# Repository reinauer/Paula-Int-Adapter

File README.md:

# Paula Interrupt Adapter

This is an Interrupt Adapter for the Amiga 500/2000 version of Paula.

## About

This adapter is an el cheapo version of the Action Replay. In connection with
the HRTMon software you can enter a debugger / monitor at any time while your
software is running, and mess around with all of memory (infinite lives, yay!)

## But Why?

I probably started getting into soldering because I wanted to have one of
[highpuff's INT7 adapters](https://www.ikod.se/a1200-600-int7/) but I could
not buy one from him, simply because the cost of shipping across the Atlantic
Ocean would by far exceed the value of the adapter. So I ordered a few PCBs
from across the Pacific instead and started soldering PLCC-52 sockets and
diodes.

Now, a few months later, I also got an Amiga 500 in my collection, and there
didn't seem to be a solution like highpuff's adapter available for the most
popular of all Amigas. So, I decided to make one.

## Bill of Materials

Here's the [Bill of Materials (BOM)](https://htmlpreview.github.io/?https://raw.githubusercontent.com/reinauer/Paula-Int-Adapter/main/bom.html).

## Make your own

* [PCBWay](https://www.pcbway.com/project/shareproject/Paula_Interrupt_Adapter__A500_A2000_.html)
* [OSHpark](https://oshpark.com/shared_projects/0WhlMhrr)

## Credits

Big thanks to djbase for the inspiration and to highpuff for the A1200/A4000
INT7 adapter

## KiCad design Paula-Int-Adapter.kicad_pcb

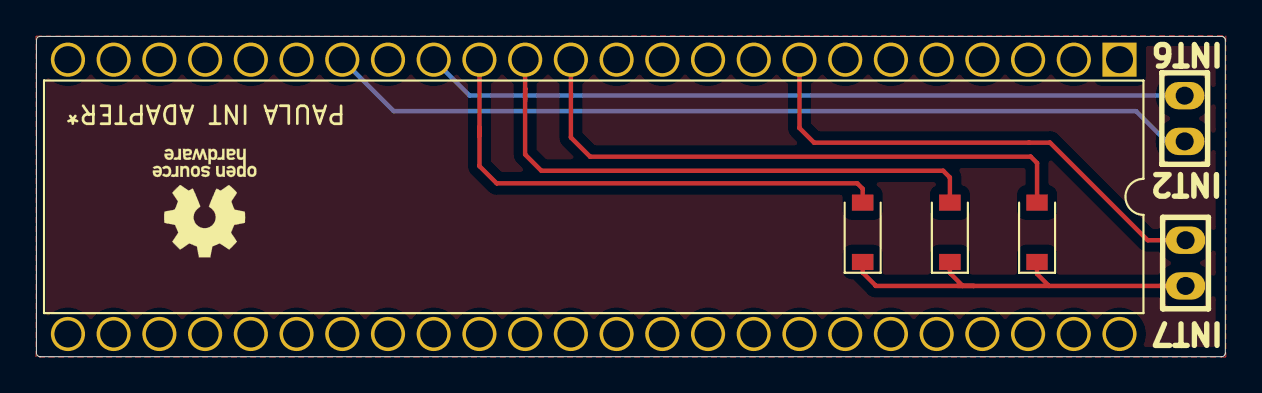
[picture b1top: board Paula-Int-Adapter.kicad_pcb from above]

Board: 2 copper layers, 66.1 x 17.8 mm, 6 parts (0 on the bottom side), 7 nets.

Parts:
D1, D2, D3: 1N4148; D_SOD-123
J1, J2: Conn_01x02; pin_strip_2
U?1: PAULA; DIP-48_W15.24mm

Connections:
unnamed: D1.1, D2.1, D3.1, J1.2
unnamed: D1.2, U?1.13
unnamed: D2.2, U?1.14
unnamed: D3.2, U?1.15
unnamed: J1.1, U?1.8
unnamed: J2.1, U?1.18
unnamed: J2.2, U?1.16

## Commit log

2021-03-16 Initial Version: Amiga 500/2000 Paula Int Adapter

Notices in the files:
Paula-Int-Adapter.kicad_pcb:
Copyright 2021 by Stefan Reinauer
